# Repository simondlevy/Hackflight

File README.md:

# Intro

Hackflight is a minimalist software toolkit for building multirotor flight
controllers and simulators.  It is geared toward people like me who want to
tinker with flight-control firmware, and use it to teach students about ideas
like
[state estimation](https://simondlevy.github.io/ekf-tutorial)
and
[PID control](https://en.wikipedia.org/wiki/Proportional%E2%80%93integral%E2%80%93derivative_controller).
<b>If you are in the 99% percent of
users who just want to get your vehicle flying without getting into firmware
hacking, I recommend [Betaflight](http://betaflight.com/)</b> (great for
getting started when you're on a budget)
<b>the [Ardupilot](http://copter.ardupilot.org) system</b> (for
sophisticated mission planning with waypoint navigation and the like), or
the <b>[Crazyflie](https://www.bitcraze.io/products/old-products/crazyflie-2-1/)</b>
platform, for a safe, inexpensive introduction to quadcopters as a research
platform.   In addition to big user communities and loads of great features,
these platforms have safety mechanisms that Hackflight lacks, which will help
avoid injury to you and damage to your vehicle.

# Design principles

Hackflight attempts to maintain a simple relationship between
the code and the elements of the flight-control dataflow diagram shown below.
Boxes represent data, ovals represent functions, and feedback arrows
represent the need for functions that have state; for
example, the maintenance of an error integral in a PID controller:

By using header-only C++ classes whenever possible, avoiding C-style macros,
[null pointers](https://www.infoq.com/presentations/Null-References-The-Billion-Dollar-Mistake-Tony-Hoare/),
inheritance, and mutation in favor of
[functional style](https://queue.acm.org/detail.cfm?id=2038036i),
and relying on existing Arduino libraries for sensors and actuators,
Hackflight supports a
[composable](https://www.progress.com/blogs/what-composability-why-should-you-care)
approach to taming the complexity of flight control. The Hackflight [codebase](src/) is
under 3,000 lines of code.

# Hardware

* MCU: [Teensy4.0](https://www.pjrc.com/store/teensy40.html)

* IMU: [BMI088 I^2C breakout board](https://www.tindie.com/products/bobbiebots/bmi088-i2c-breakout)

* Receiver: [OMGS3 ESP32](https://unexpectedmaker.com/shop.html#!/OMGS3/p/687192227)

* Transmitter: Radiomaster T8L modified with [custom circuit board](kicad/tx) using
[TinyS3 ESP32](https://www.adafruit.com/product/5398)

* Telemetry dongle: [TinyPICO ESP32](https://www.adafruit.com/product/5028)

# Simulator

For flight simulation, Hackflight uses [Webots](https://cyberbotics.com/),
a free, open-source robotics simulator. Click [here](webots/apex2) to get started.

# Citing Hackflight

Please cite Hackflight as:

```
@ARTICLE{10.3389/fnbot.2020.00016,
AUTHOR={Levy, Simon D.},   
TITLE={Robustness Through Simplicity: A Minimalist Gateway to Neurorobotic Flight},      
JOURNAL={Frontiers in Neurorobotics},      
VOLUME={14},           
YEAR={2020},      
URL={https://www.frontiersin.org/articles/10.3389/fnbot.2020.00016},       
DOI={10.3389/fnbot.2020.00016},      
ISSN={1662-5218}
}
```

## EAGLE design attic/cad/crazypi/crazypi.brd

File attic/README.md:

# Intro

Hackflight is a minimalist software toolkit for building multirotor flight
controllers and simulators.  It is geared toward people like me who want to
tinker with flight-control firmware, and use it to teach students about ideas
like
[state estimation](https://simondlevy.github.io/ekf-tutorial)
and
[PID control](https://en.wikipedia.org/wiki/Proportional%E2%80%93integral%E2%80%93derivative_controller).
<b>If you are in the 99% percent of
users who just want to get your vehicle flying without getting into firmware
hacking, I recommend [Betaflight](http://betaflight.com/)</b> (great for
getting started when you're on a budget)
<b>the [Ardupilot](http://copter.ardupilot.org) system</b> (for
sophisticated mission planning with waypoint navigation and the like), or
the <b>[Crazyflie](https://www.bitcraze.io/products/old-products/crazyflie-2-1/)</b>
platform, for a safe, inexpensive introduction to quadcopters as a research
platform.   In addition to big user communities and loads of great features,
these platforms have safety mechanisms that Hackflight lacks, which will help
avoid injury to you and damage to your vehicle.

# Design principles

Hackflight attempts to maintain a simple relationship between
the code and the elements of the flight-control dataflow diagram shown below.
Boxes represent data, ovals represent functions, and feedback arrows
represent the need for functions that have state (instance variables); for
example, the maintenance of an error integral in a PID controller:

By using header-only C++ classes whenever possible, avoiding C-style macros and 
[null pointers](https://www.infoq.com/presentations/Null-References-The-Billion-Dollar-Mistake-Tony-Hoare/),
and relying on existing Arduino libraries for sensors and actuators,
Hackflight supports a [composable](https://www.progress.com/blogs/what-composability-why-should-you-care) 
approach to taming the complexity of flight control. The Hackflight [codebase](src/) is
around 3,000 lines of code.

# Hardware

Hackflight currently runs on a custom-built micro [quadcopter](media/boltquad2.jpg) that uses 
the [Crazyfle Bolt 1.1](https://www.bitcraze.io/products/crazyflie-bolt-1-1/)
flight controller for state estimation and PID control, and a
[BlueSMIRF v2](https://www.sparkfun.com/sparkfun-bluesmirf-v2.html) for 
remote control and logging.

# Simulator

For flight simulation, Hackflight uses [Webots](https://cyberbotics.com/),
a free, open-source robotics simulator. Click [here](webots) to get started.

# Haskell support

If you [love Haskell](https://koerbitz.me/posts/Why-I-love-Haskell.html) as much
as I do and want to see how it can be used for flight control, click [here](haskell).

# Citing Hackflight

Please cite Hackflight as:

```
@ARTICLE{10.3389/fnbot.2020.00016,
AUTHOR={Levy, Simon D.},   
TITLE={Robustness Through Simplicity: A Minimalist Gateway to Neurorobotic Flight},      
JOURNAL={Frontiers in Neurorobotics},      
VOLUME={14},           
YEAR={2020},      
URL={https://www.frontiersin.org/articles/10.3389/fnbot.2020.00016},       
DOI={10.3389/fnbot.2020.00016},      
ISSN={1662-5218}
}
```

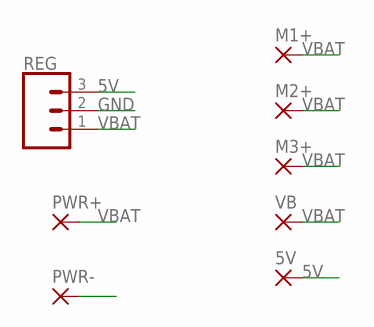
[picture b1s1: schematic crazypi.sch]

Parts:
5V: SMD2; SMD1,27-2,54
M1+, M2+, M3+: SMD2; SMD1,27-2,54
PWR+: SMD5; SMD2,54-5,08
PWR-: SMD5; SMD2,54-5,08
REG: CONN_031X03_NO_SILK; 1X03_NO_SILK
VB: SMD2; SMD1,27-2,54

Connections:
5V: 5V.1, REG.3
GND: PWR-.1, REG.2
VBAT: M1+.1, M2+.1, M3+.1, PWR+.1, REG.1, VB.1

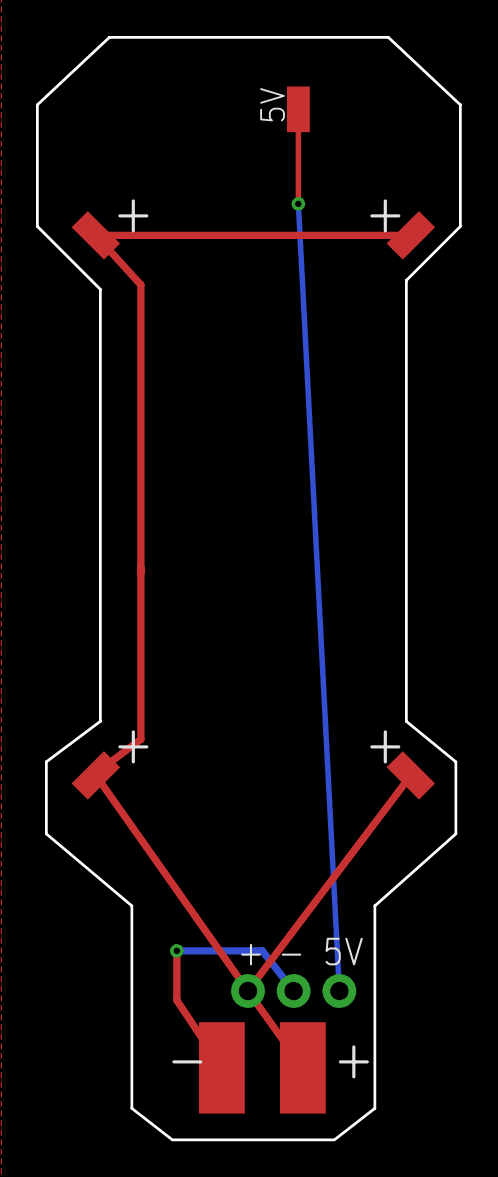
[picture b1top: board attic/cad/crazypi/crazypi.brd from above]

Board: 2 copper layers, 23.5 x 61.2 mm, 8 parts (0 on the bottom side), 3 nets.

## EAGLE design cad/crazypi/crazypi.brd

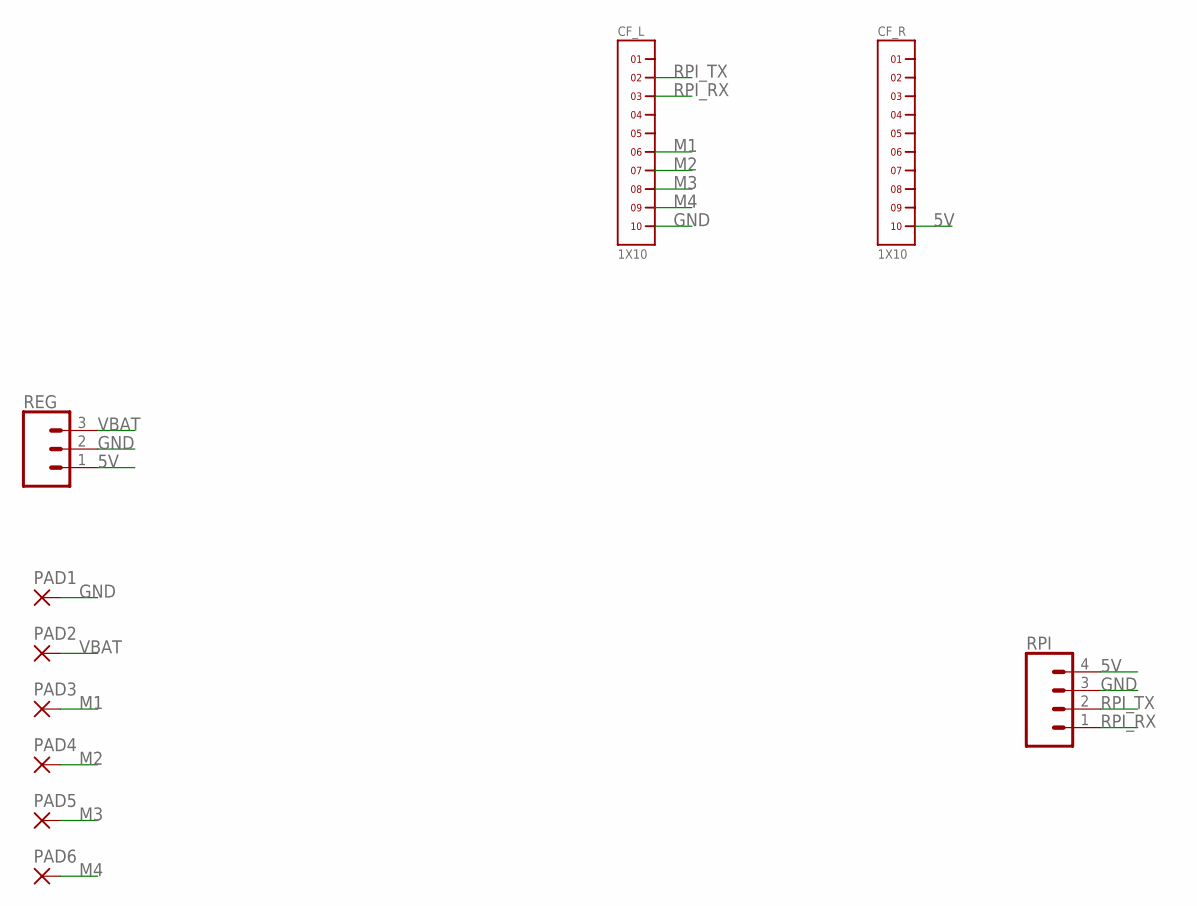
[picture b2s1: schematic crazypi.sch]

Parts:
CF_L: 1X10
CF_R: 1X10
PAD1, PAD2, PAD3, PAD4, PAD5, PAD6: SMD2; SMD1,27-2,54
REG: CONN_031X03_NO_SILK; 1X03_NO_SILK
RPI: CONN_041X04_NO_SILK; 1X04_NO_SILK

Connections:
5V: CF_R.10, REG.1, RPI.4
GND: CF_L.10, PAD1.1, REG.2, RPI.3
M1: CF_L.6, PAD3.1
M2: CF_L.7, PAD4.1
M3: CF_L.8, PAD5.1
M4: CF_L.9, PAD6.1
RPI_RX: CF_L.3, RPI.1
RPI_TX: CF_L.2, RPI.2
VBAT: PAD2.1, REG.3

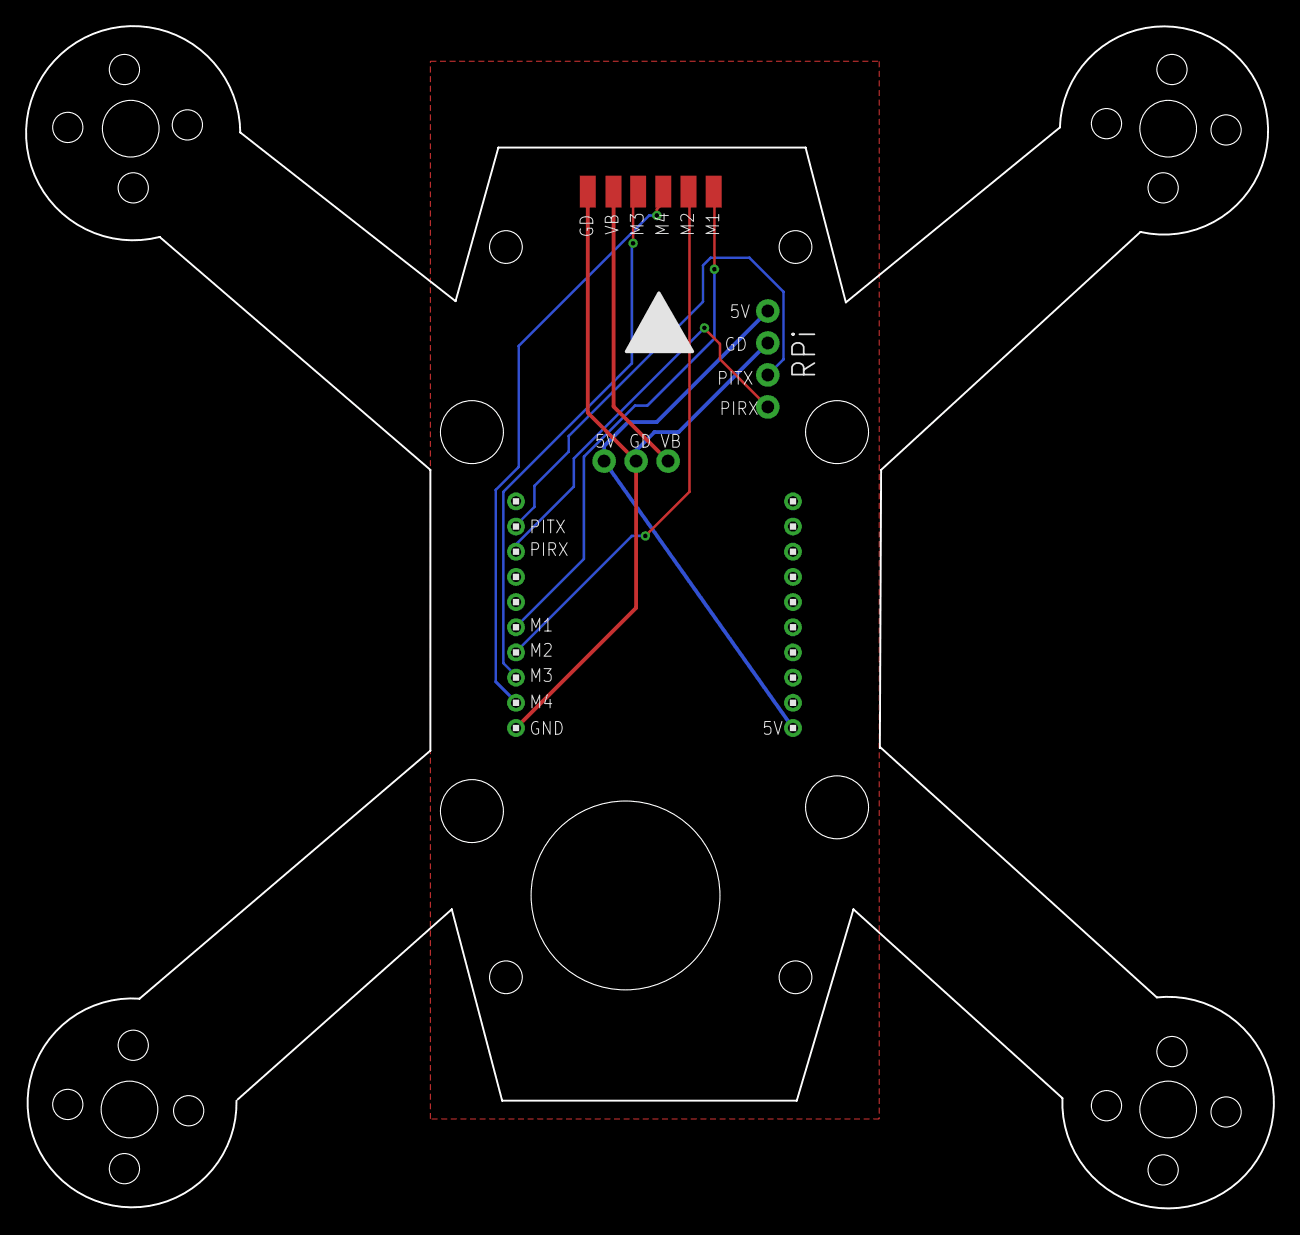
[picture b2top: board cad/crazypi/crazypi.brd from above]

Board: 2 copper layers, 99.1 x 93.9 mm, 10 parts (0 on the bottom side), 9 nets.

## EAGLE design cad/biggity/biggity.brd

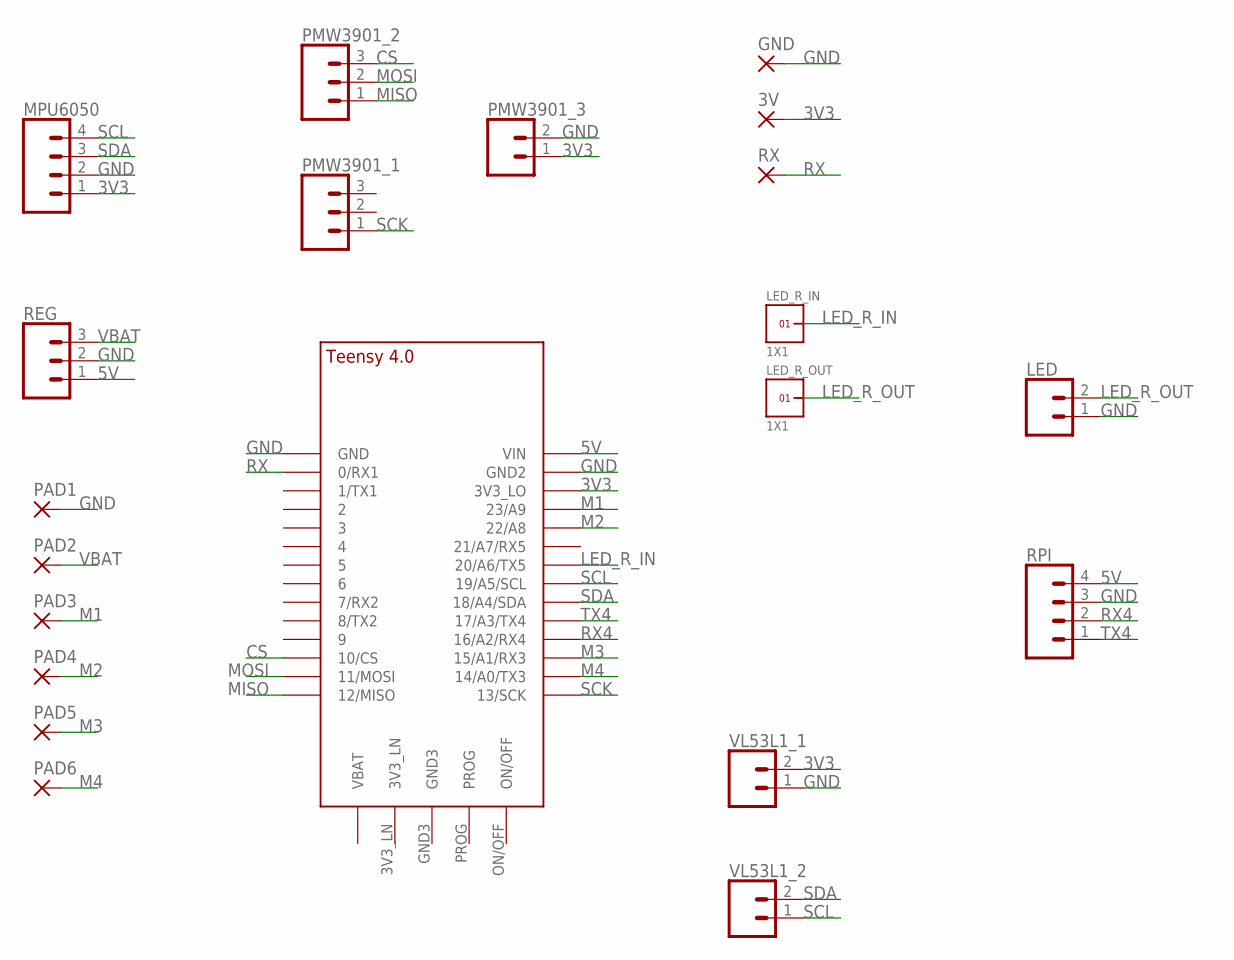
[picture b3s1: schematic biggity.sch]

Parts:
3V: SMD2; SMD1,27-2,54
GND: SMD2; SMD1,27-2,54
LED: CONN_021X02_NO_SILK; 1X02_NO_SILK
LED_R_IN: 1X1
LED_R_OUT: 1X1
MPU6050: CONN_041X04_NO_SILK; 1X04_NO_SILK
PAD1, PAD2, PAD3, PAD4, PAD5, PAD6: SMD2; SMD1,27-2,54
PMW3901_1, PMW3901_2: CONN_031X03_NO_SILK; 1X03_NO_SILK
PMW3901_3: CONN_021X02_NO_SILK; 1X02_NO_SILK
REG: CONN_031X03_NO_SILK; 1X03_NO_SILK
RPI: CONN_041X04_NO_SILK; 1X04_NO_SILK
RX: SMD2; SMD1,27-2,54
U$1: TEENSY_4.0
VL53L1_1, VL53L1_2: CONN_021X02_NO_SILK; 1X02_NO_SILK

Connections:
3V3: 3V.1, MPU6050.1, PMW3901_3.1, U$1.3V3_LO, VL53L1_1.2
5V: REG.1, RPI.4, U$1.VIN
CS: PMW3901_2.3, U$1.10/CS
GND: GND.1, LED.1, MPU6050.2, PAD1.1, PMW3901_3.2, REG.2, RPI.3, U$1.GND, U$1.GND2, VL53L1_1.1
LED_R_IN: LED_R_IN.1, U$1.20/A6 (20/A6/TX5)
LED_R_OUT: LED.2, LED_R_OUT.1
M1: PAD3.1, U$1.23/A9
M2: PAD4.1, U$1.22/A8
M3: PAD5.1, U$1.15/A1 (15/A1/RX3)
M4: PAD6.1, U$1.14/A0 (14/A0/TX3)
MISO: PMW3901_2.1, U$1.12/MISO
MOSI: PMW3901_2.2, U$1.11/MOSI
RX: RX.1, U$1.0/RX (0/RX1)
RX4: RPI.2, U$1.16/A2 (16/A2/RX4)
SCK: PMW3901_1.1, U$1.13/SCK
SCL: MPU6050.4, U$1.19/A5/SCL, VL53L1_2.1
SDA: MPU6050.3, U$1.18/A4/SDA, VL53L1_2.2
TX4: RPI.1, U$1.17/A3 (17/A3/TX4)
VBAT: PAD2.1, REG.3

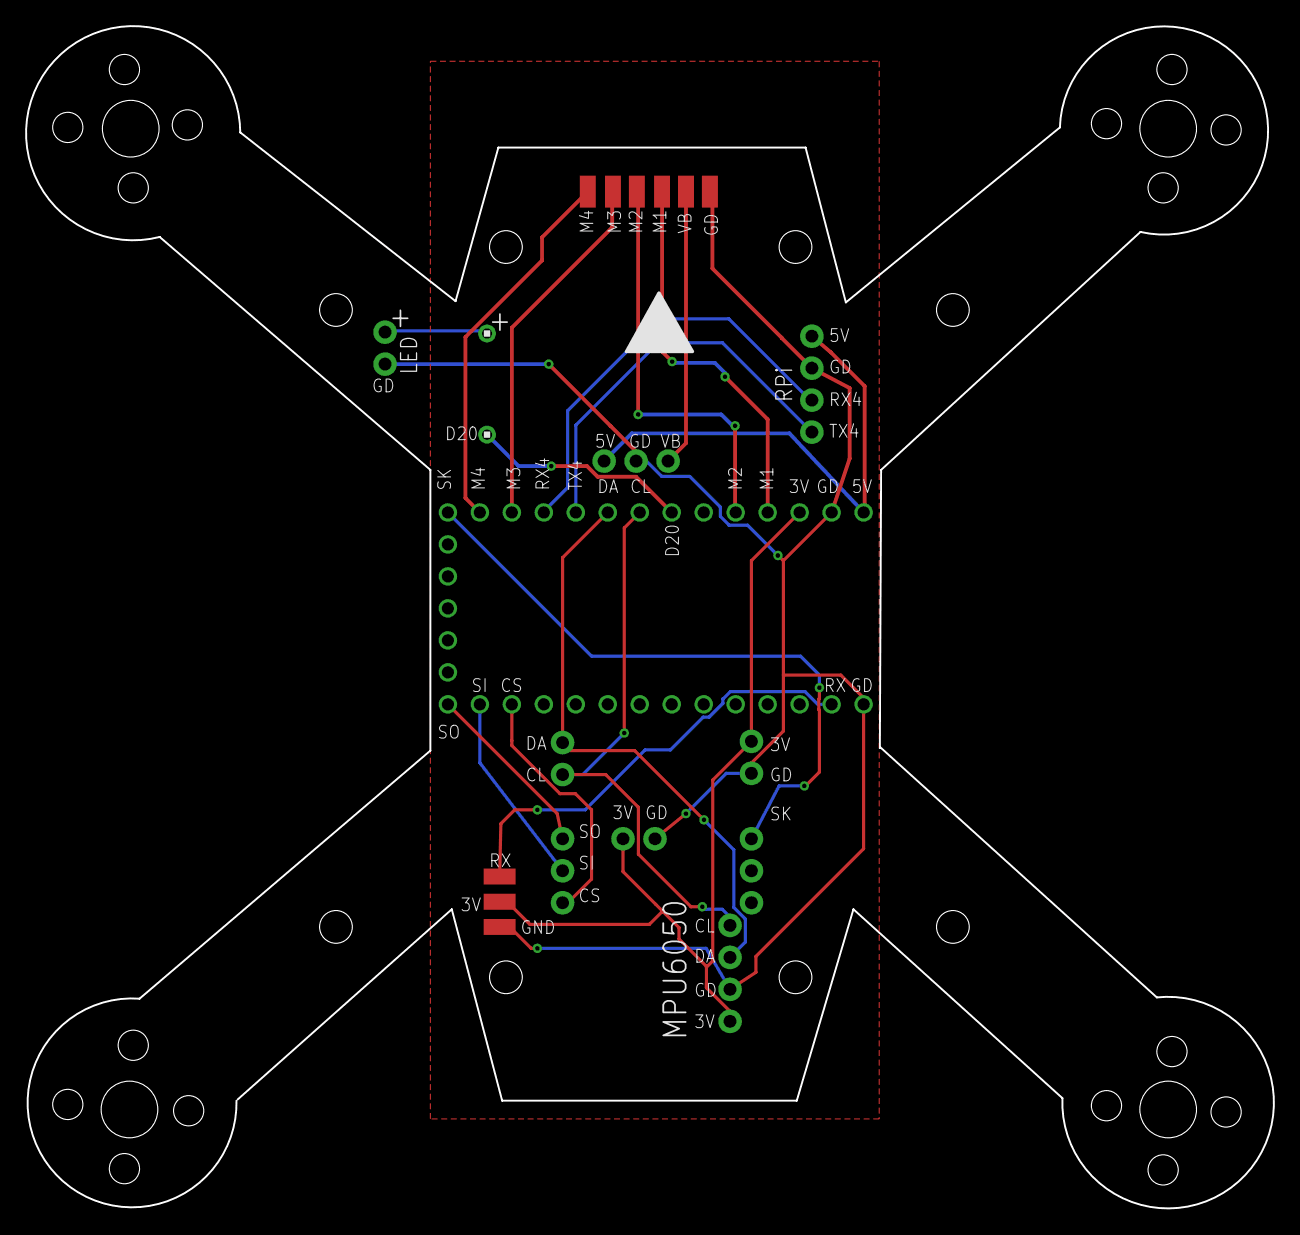
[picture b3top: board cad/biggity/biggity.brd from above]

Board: 2 copper layers, 99.1 x 93.9 mm, 21 parts (1 on the bottom side), 19 nets.

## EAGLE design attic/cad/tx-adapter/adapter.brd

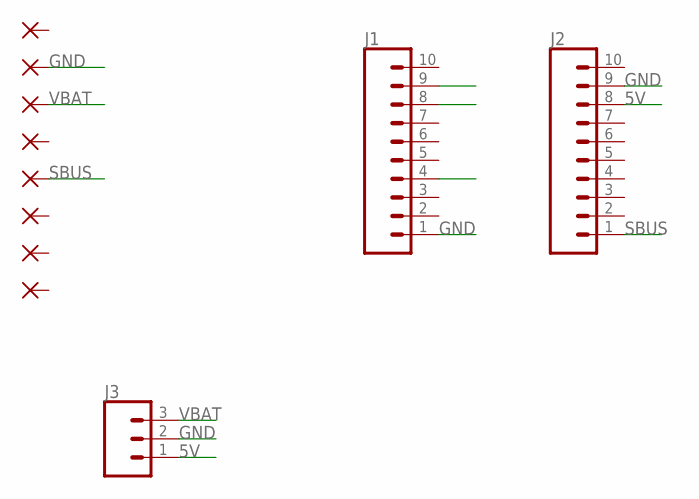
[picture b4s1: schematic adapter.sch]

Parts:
GND: SMD2; SMD1,27-2,54
J1, J2: CONN_10NO_SILK_PTH_FEMALE; 1X10_NO_SILK
J3: CONN_031X03_NO_SILK; 1X03_NO_SILK
PAD1, PAD2, PAD3, PAD4, PAD5: SMD2; SMD1,27-2,54
SBUS: SMD2; SMD1,27-2,54
VBAT: SMD2; SMD1,27-2,54

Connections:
3V3: J1.4
5V: J2.8, J3.1
GND: GND.1, J1.1, J2.9, J3.2
M2: J1.9
M3: J1.8
SBUS: J2.1, SBUS.1
VBAT: J3.3, VBAT.1

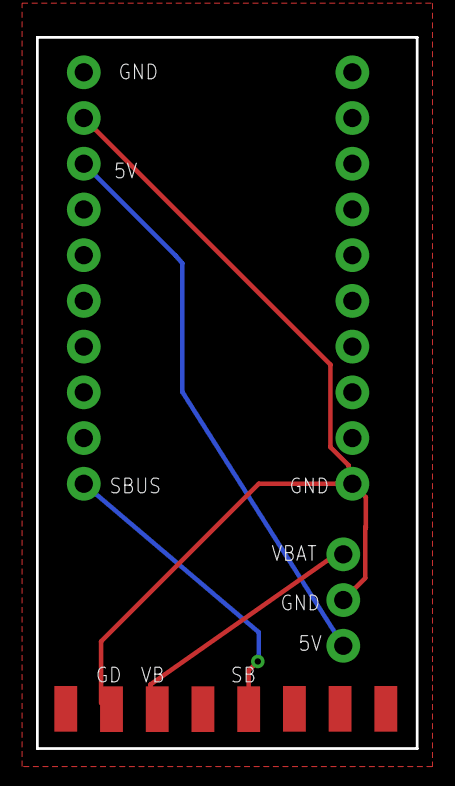
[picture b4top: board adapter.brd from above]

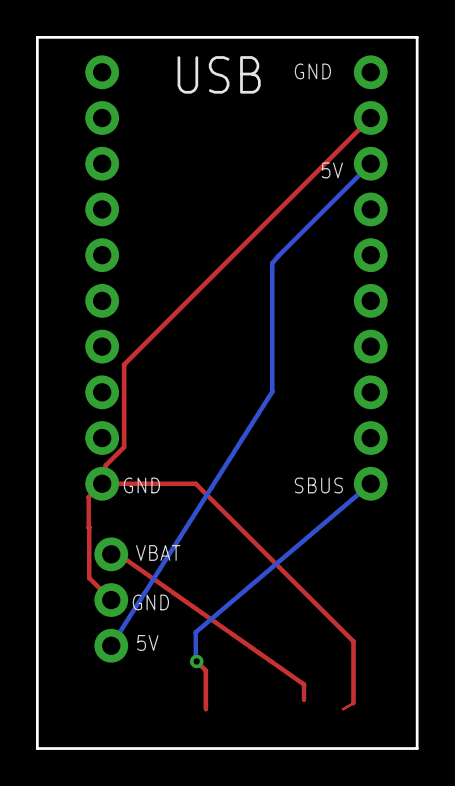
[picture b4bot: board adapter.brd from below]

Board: 2 copper layers, 21.1 x 39.5 mm, 11 parts (2 on the bottom side), 4 nets.

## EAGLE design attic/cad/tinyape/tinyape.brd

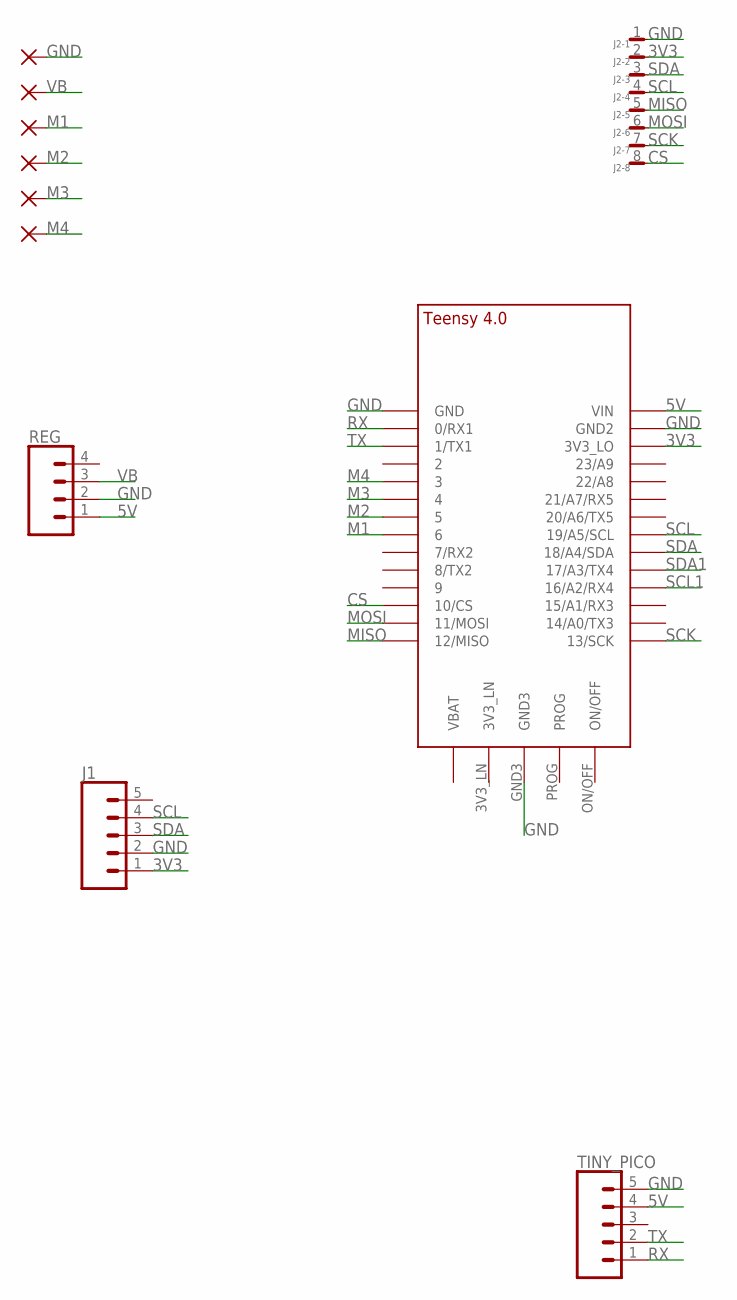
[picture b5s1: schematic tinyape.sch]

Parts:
GND: SMD2; SMD1,27-2,54
J1: CONN_05NO_SILK; 1X05_NO_SILK
J2: JST-SH-8_RA; SM08B-SRSS-TB
M1, M2, M3, M4: SMD2; SMD1,27-2,54
REG: CONN_041X04_NO_SILK; 1X04_NO_SILK
TINY_PICO: CONN_05NO_SILK; 1X05_NO_SILK
U$1: TEENSY_4.0
VBAT: SMD2; SMD1,27-2,54

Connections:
3V3: J1.1, J2.2, U$1.3V3_LO
5V: REG.1, TINY_PICO.4, U$1.VIN
CS: J2.8, U$1.10/CS
GND: GND.1, J1.2, J2.1, REG.2, TINY_PICO.5, U$1.GND, U$1.GND2, U$1.GND3
M1: M4.1, U$1.6
M2: M3.1, U$1.5
M3: M2.1, U$1.4/CANRX (4)
M4: M1.1, U$1.3/CANTX (3)
MISO: J2.5, U$1.12/MISO
MOSI: J2.6, U$1.11/MOSI
RX: TINY_PICO.1, U$1.0/RX (0/RX1)
SCK: J2.7, U$1.13/SCK
SCL: J1.4, J2.4, U$1.19/A5/SCL
SCL1: U$1.16/A2 (16/A2/RX4)
SDA: J1.3, J2.3, U$1.18/A4/SDA
SDA1: U$1.17/A3 (17/A3/TX4)
TX: TINY_PICO.2, U$1.1/TX (1/TX1)
VB: REG.3, VBAT.1

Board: 2 copper layers, 11 parts (2 on the bottom side), 16 nets, no tracks yet.

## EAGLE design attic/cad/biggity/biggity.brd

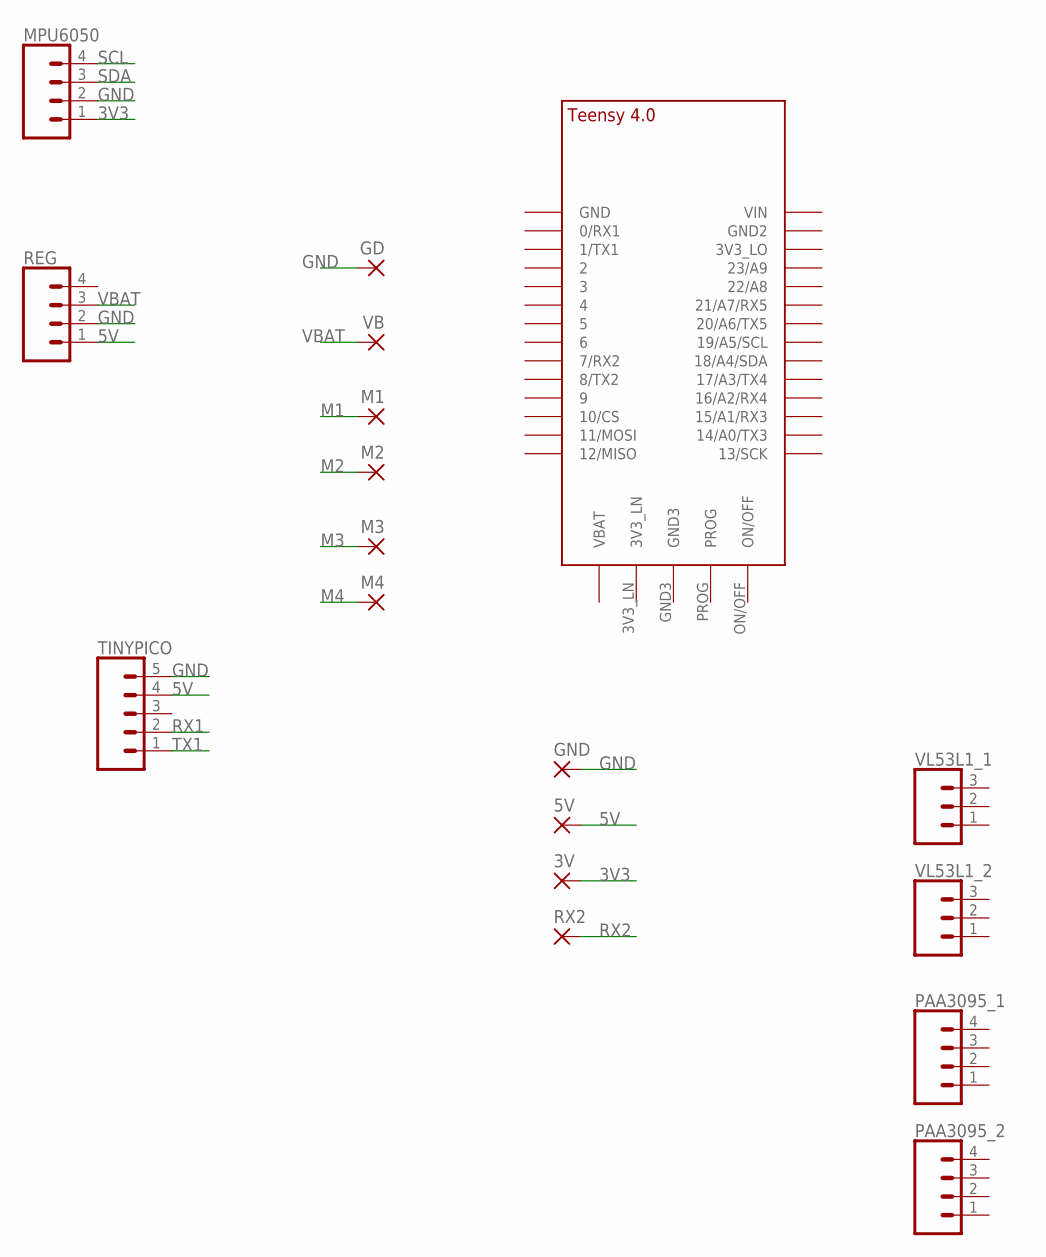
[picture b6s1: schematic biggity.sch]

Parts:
3V, 5V: SMD2; SMD1,27-2,54
GD: SMD2; SMD1,27-2,54
GND: SMD2; SMD1,27-2,54
M1, M2, M3, M4: SMD2; SMD1,27-2,54
MPU6050: CONN_041X04_NO_SILK; 1X04_NO_SILK
PAA3095_1, PAA3095_2: CONN_041X04_NO_SILK; 1X04_NO_SILK
REG: CONN_041X04_NO_SILK; 1X04_NO_SILK
RX2: SMD2; SMD1,27-2,54
TINYPICO: CONN_05NO_SILK; 1X05_NO_SILK
U$1: TEENSY_4.0
VB: SMD2; SMD1,27-2,54
VL53L1_1, VL53L1_2: CONN_031X03_NO_SILK; 1X03_NO_SILK

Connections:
3V3: 3V.1, MPU6050.1
5V: 5V.1, REG.1, TINYPICO.4
GND: GD.1, GND.1, MPU6050.2, REG.2, TINYPICO.5
M1: M1.1
M2: M2.1
M3: M3.1
M4: M4.1
RX1: TINYPICO.2
RX2: RX2.1
SCL: MPU6050.4
SDA: MPU6050.3
TX1: TINYPICO.1
VBAT: REG.3, VB.1

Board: 2 copper layers, 18 parts (1 on the bottom side), 4 nets, no tracks yet.

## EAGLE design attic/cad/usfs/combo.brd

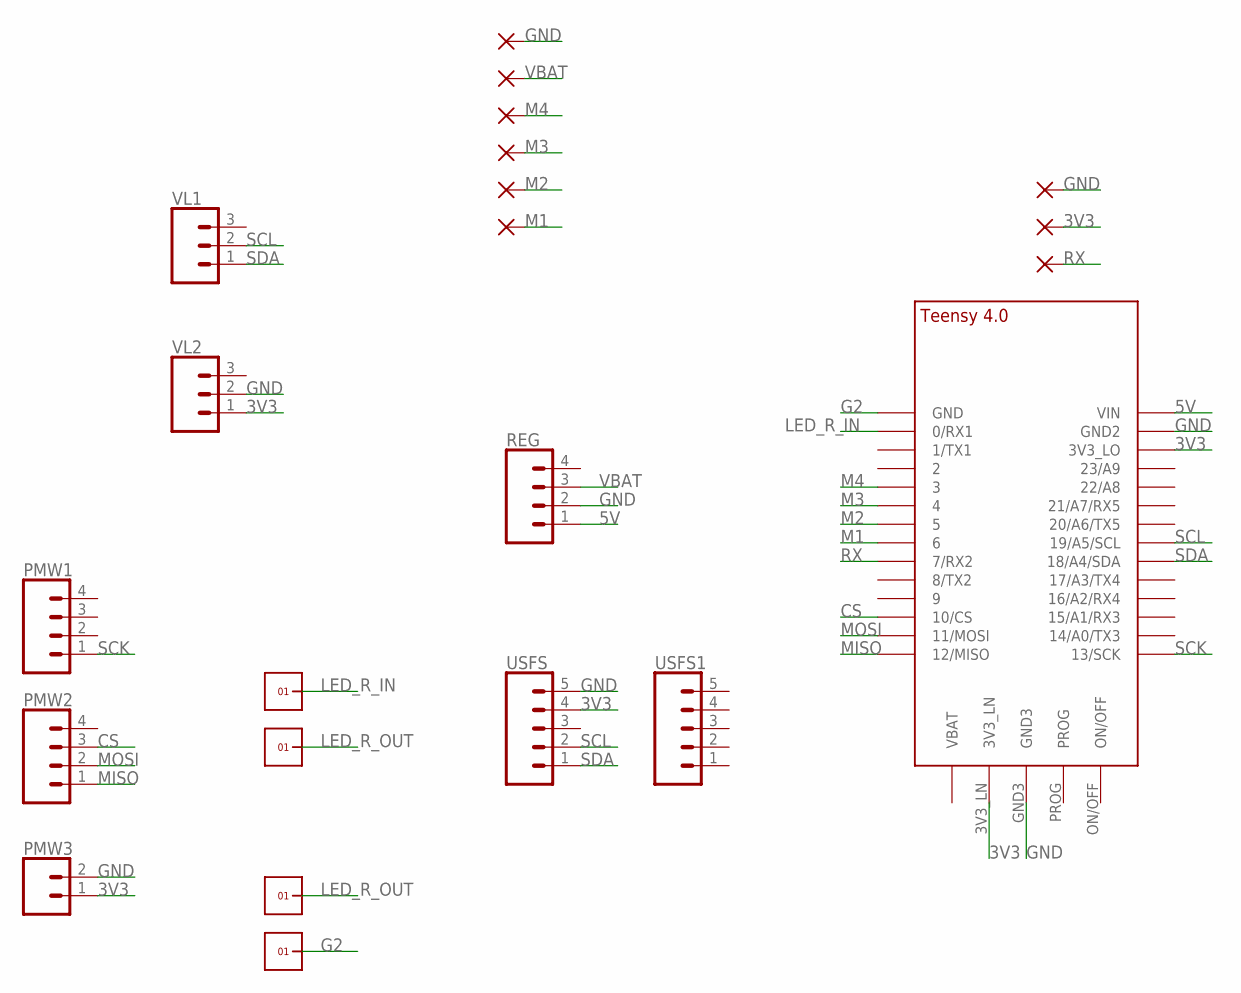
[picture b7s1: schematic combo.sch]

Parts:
3V: SMD2; SMD1,27-2,54
GD: SMD2; SMD1,27-2,54
GND: SMD2; SMD1,27-2,54
M1, M2, M3, M4: SMD2; SMD1,27-2,54
PMW1, PMW2: CONN_041X04_NO_SILK; 1X04_NO_SILK
PMW3: CONN_021X02_NO_SILK; 1X02_NO_SILK
REG: CONN_041X04_NO_SILK; 1X04_NO_SILK
RX: SMD2; SMD1,27-2,54
U$1: TEENSY_4.0
U$3, U$4, U$6, U$7: 1X1
USFS, USFS1: CONN_05NO_SILK; 1X05_NO_SILK
VBAT: SMD2; SMD1,27-2,54
VL1, VL2: CONN_031X03_NO_SILK; 1X03_NO_SILK

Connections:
3V3: 3V.1, PMW3.1, U$1.3V3_LN, U$1.3V3_LO, USFS.4, VL2.1
5V: REG.1, U$1.VIN
CS: PMW2.3, U$1.10/CS
G2: U$1.GND, U$7.1
GND: GD.1, GND.1, PMW3.2, REG.2, U$1.GND2, U$1.GND3, USFS.5, VL2.2
LED_R_IN: U$1.0/RX (0/RX1), U$3.1
LED_R_OUT: U$4.1, U$6.1
M1: M1.1, U$1.6
M2: M2.1, U$1.5
M3: M3.1, U$1.4/CANRX (4)
M4: M4.1, U$1.3/CANTX (3)
MISO: PMW2.1, U$1.12/MISO
MOSI: PMW2.2, U$1.11/MOSI
RX: RX.1, U$1.7 (7/RX2)
SCK: PMW1.1, U$1.13/SCK
SCL: U$1.19/A5/SCL, USFS.2, VL1.2
SDA: U$1.18/A4/SDA, USFS.1, VL1.1
VBAT: REG.3, VBAT.1

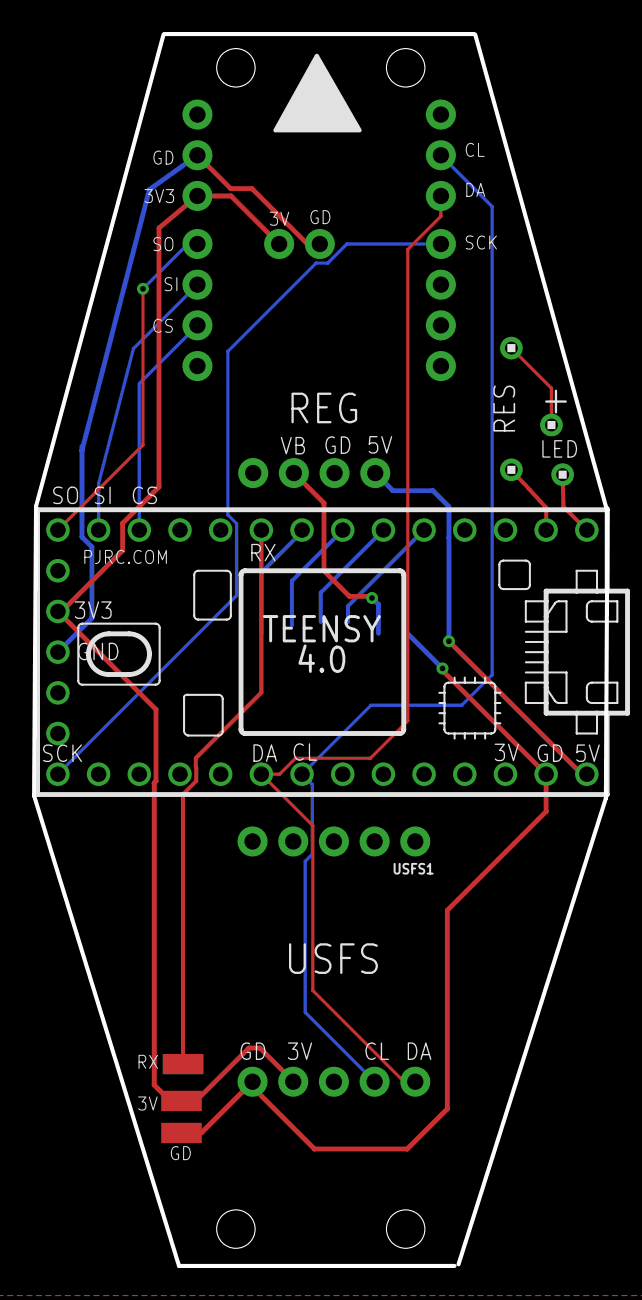
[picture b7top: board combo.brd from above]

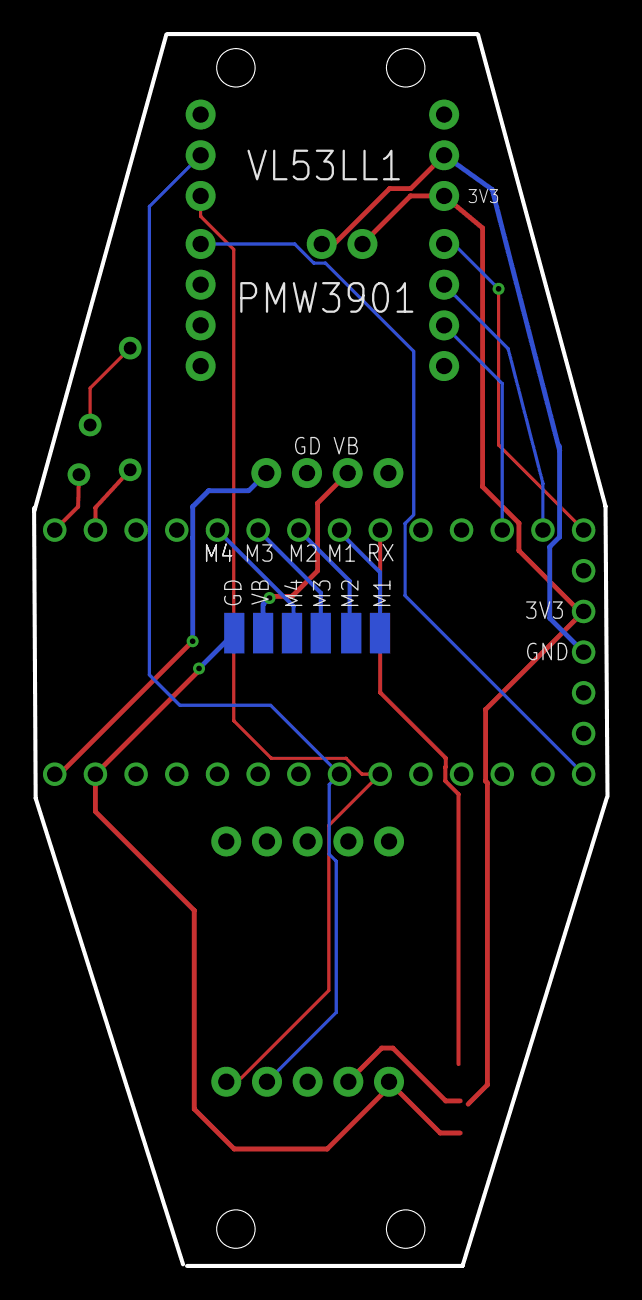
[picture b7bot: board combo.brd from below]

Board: 2 copper layers, 35.8 x 76.9 mm, 22 parts (6 on the bottom side), 18 nets.

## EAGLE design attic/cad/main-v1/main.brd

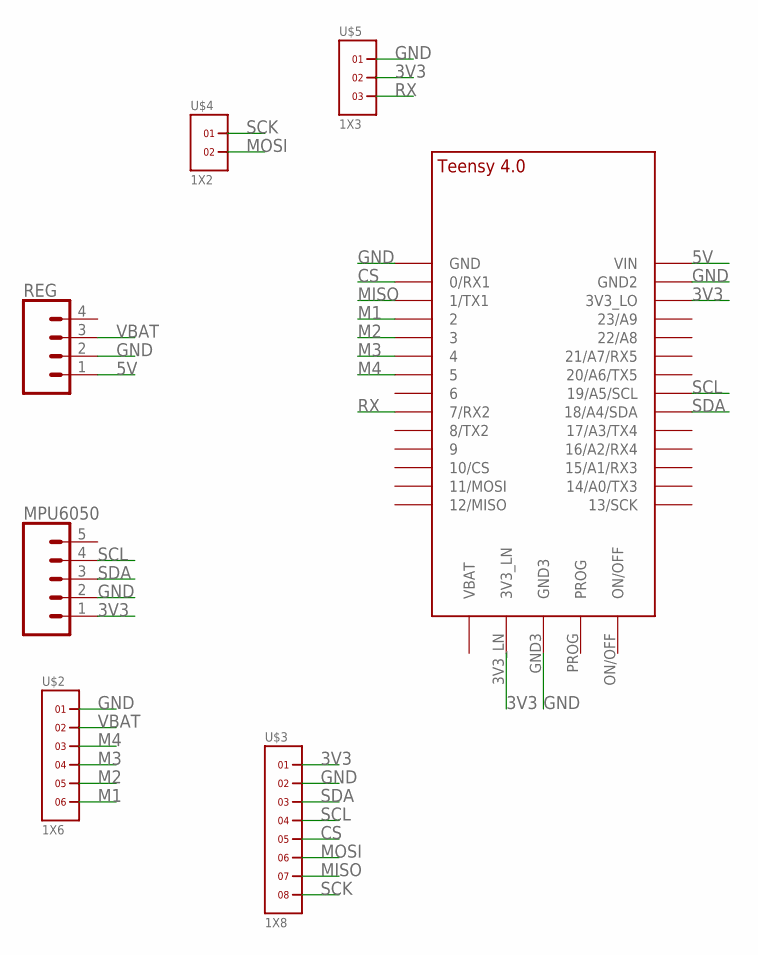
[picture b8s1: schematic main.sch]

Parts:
MPU6050: CONN_05NO_SILK; 1X05_NO_SILK
REG: CONN_041X04_NO_SILK; 1X04_NO_SILK
U$1: TEENSY_4.0
U$2: 1X6
U$3: 1X8
U$4: 1X2
U$5: 1X3

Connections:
3V3: MPU6050.1, U$1.3V3_LN, U$1.3V3_LO, U$3.1, U$5.2
5V: REG.1, U$1.VIN
CS: U$1.0/RX (0/RX1), U$3.5
GND: MPU6050.2, REG.2, U$1.GND, U$1.GND2, U$1.GND3, U$2.1, U$3.2, U$5.1
M1: U$1.2, U$2.6
M2: U$1.3/CANTX (3), U$2.5
M3: U$1.4/CANRX (4), U$2.4
M4: U$1.5, U$2.3
MISO: U$1.1/TX (1/TX1), U$3.7
MOSI: U$3.6, U$4.2
RX: U$1.7 (7/RX2), U$5.3
SCK: U$3.8, U$4.1
SCL: MPU6050.4, U$1.19/A5/SCL, U$3.4
SDA: MPU6050.3, U$1.18/A4/SDA, U$3.3
VBAT: REG.3, U$2.2

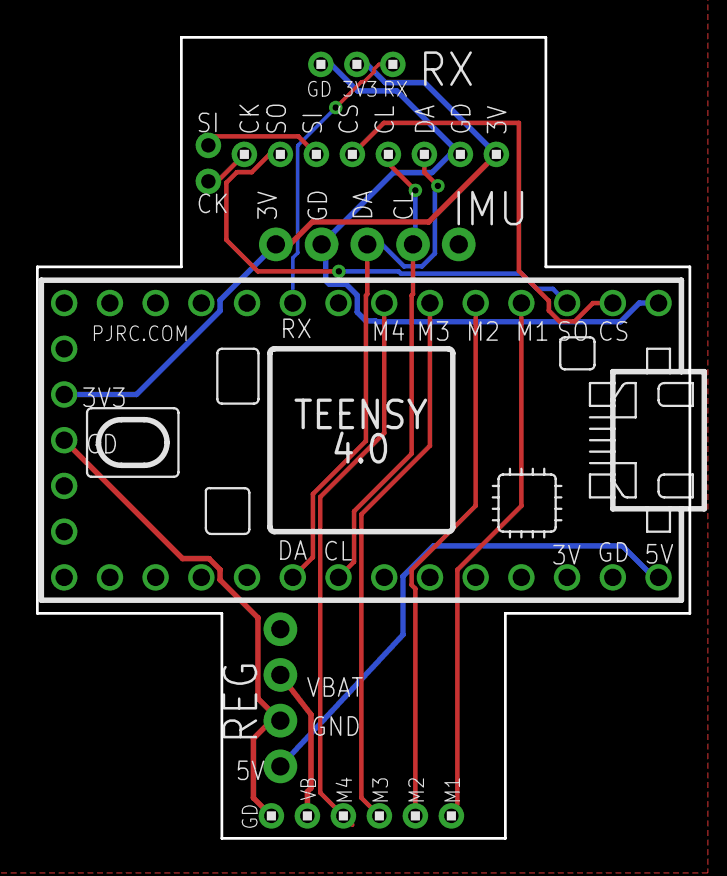
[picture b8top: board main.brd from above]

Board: 2 copper layers, 36.2 x 44.5 mm, 7 parts (1 on the bottom side), 15 nets.

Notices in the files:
parts and their libraries:
SparkFun-Connectors: Licensing: Creative Commons ShareAlike 4.0 International - https://creativecommons.org/licenses/by-sa/4.0
